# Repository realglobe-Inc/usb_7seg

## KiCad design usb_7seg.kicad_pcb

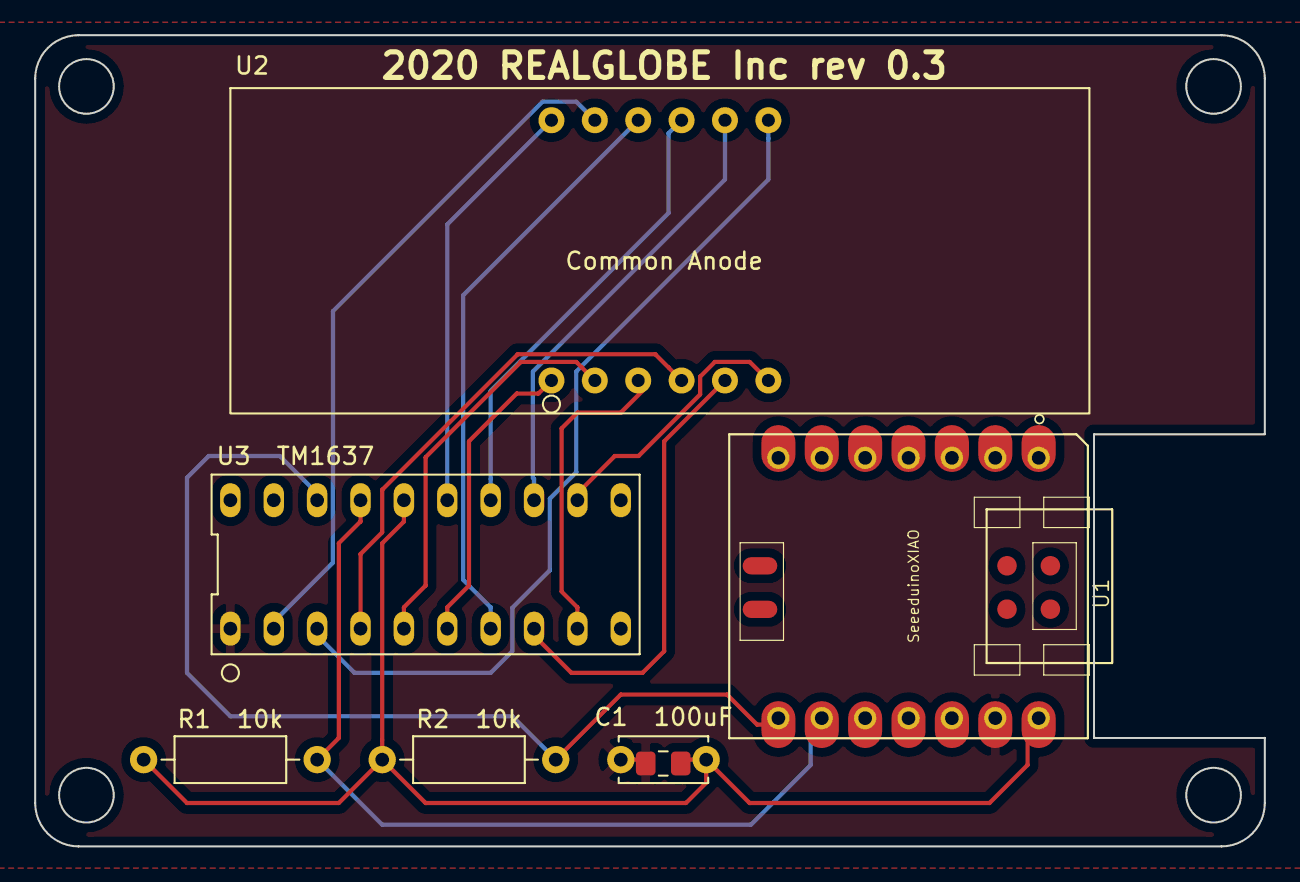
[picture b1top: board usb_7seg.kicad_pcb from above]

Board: 2 copper layers, 72.0 x 47.5 mm, 6 parts (0 on the bottom side), 16 nets.

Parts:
C1  100uF: 10uF; C_Disc_D5.0mm_W2.5mm_P5.00mm
R1  10k, R2  10k: 10k; R_Axial_DIN0207_L6.3mm_D2.5mm_P10.16mm_Horizontal
U1: SeeeduinoXIAO; SeeedXIAO
U2: 7segment_led; 7segment_led_0.56
U3  TM1637: TM1637; TM1630

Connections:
+5V: C1 100uF.2, R1 10k.1, R2 10k.1, U1.14, U3 TM1637.16
GND: C1 100uF.1, U1.13, U3 TM1637.1
unnamed: R1 10k.2, U1.9, U3 TM1637.17
unnamed: R2 10k.2, U1.8, U3 TM1637.18
unnamed: U2.1, U3 TM1637.6
unnamed: U2.2, U3 TM1637.5
unnamed: U2.3, U3 TM1637.9
unnamed: U2.4, U3 TM1637.4
unnamed: U2.5, U3 TM1637.8
unnamed: U2.6, U3 TM1637.12
unnamed: U2.7, U3 TM1637.3
unnamed: U2.8, U3 TM1637.13
unnamed: U2.9, U3 TM1637.14
unnamed: U2.10, U3 TM1637.7
unnamed: U2.11, U3 TM1637.2
unnamed: U2.12, U3 TM1637.15

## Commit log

2020-06-29 kicadの空プロジェクト
2020-06-29 回路図書いた
2020-07-01 0.36inchの7セグLEDを削除した
2020-07-01 C1,2が電源に繋がってなかった
2020-07-01 [コミット漏れ]C1,2が電源に繋がってなかった
2020-07-01 xiao以外配置配線完了
2020-07-06 基板外形決めてDRC通してとりあえず完成
2020-07-06 ガーバーデータ
2020-07-07 社名入れたり、C2,R2のシルク消したり
2020-07-08 7セグLEDを1つ削除した
2020-07-08 7セグLED1つ版の仮配置
2020-07-08 とりあえず完成。DRCもok
2020-07-08 不要なので削除
2020-07-08 ベタグラ書け忘れてた
2020-07-13 ledcontrolのサンプルソフトそのまま
2020-07-13 add vscode workspace
2020-07-20 add .vscode/
2020-07-20 とりあえず動く
2020-09-01 1秒周期で表示状態を送信するようにした。けど、バッファのゴミも出てるので修正が必要。
2020-09-02 バッファにゴミが出る問題の修正
2020-09-11 スロットマシンのサンプルを追加した
2020-09-17 シリアル出力にステータスをつけた
2020-09-19 ディジタル時計デモを実装した
2020-09-19 カウントアップタイマーが動くようになった
2020-09-20 改行をキャンセルする処理をいれた
2020-09-20 READMEにユースケースの説明を追加した
2020-09-23 sttyの説明を追加した
2020-10-30 シリアル出力の改行コードを変更した
2020-10-30 フットプリントの関連付けを修正
2020-10-30 いろいろ修正した
2020-11-16 6桁以上の数値を受信すると下位2桁が表示されてしまう問題の修正
2020-12-01 配置配線、ERC ok
2020-12-03 配線を消して、部品を仮置きした
2020-12-03 TM1637のシンボルを更新した
2020-12-08 ネットリスト大丈夫そう
2020-12-08 とりあえず配線完了 DRC ok
2020-12-08 ガーバー出力オプションを修正した
2020-12-08 7セグLEDの極性をシルクで記載した
2020-12-17 TM1637対応の為、空のスケッチにした
2020-12-17 消灯が出来ない問題を修正
2020-12-17 マジックナンバーをdefineした
2020-12-17 メインの処理を実装した
2020-12-17 テストコードを消した
2020-12-25 コーディングルールに沿ってない部分を修正した
